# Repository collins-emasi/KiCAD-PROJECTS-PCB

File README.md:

# KiCAD-PROJECTS-PCB
In this repository, I will be sharing some of the project I'm working on with KiCAD software.

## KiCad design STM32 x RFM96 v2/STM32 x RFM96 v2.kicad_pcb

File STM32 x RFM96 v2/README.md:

# STM32 X RFM96 Board
This is an STM32 based board that features semtechs LoRa Chip
Some of the features include
- USB connection
- UART, I2C peripherals
- Battery powered
- LoRa Connectivity
- Ultra low power STM32 chip

# Images

# KiCAD
I am using KiCAD v7.0

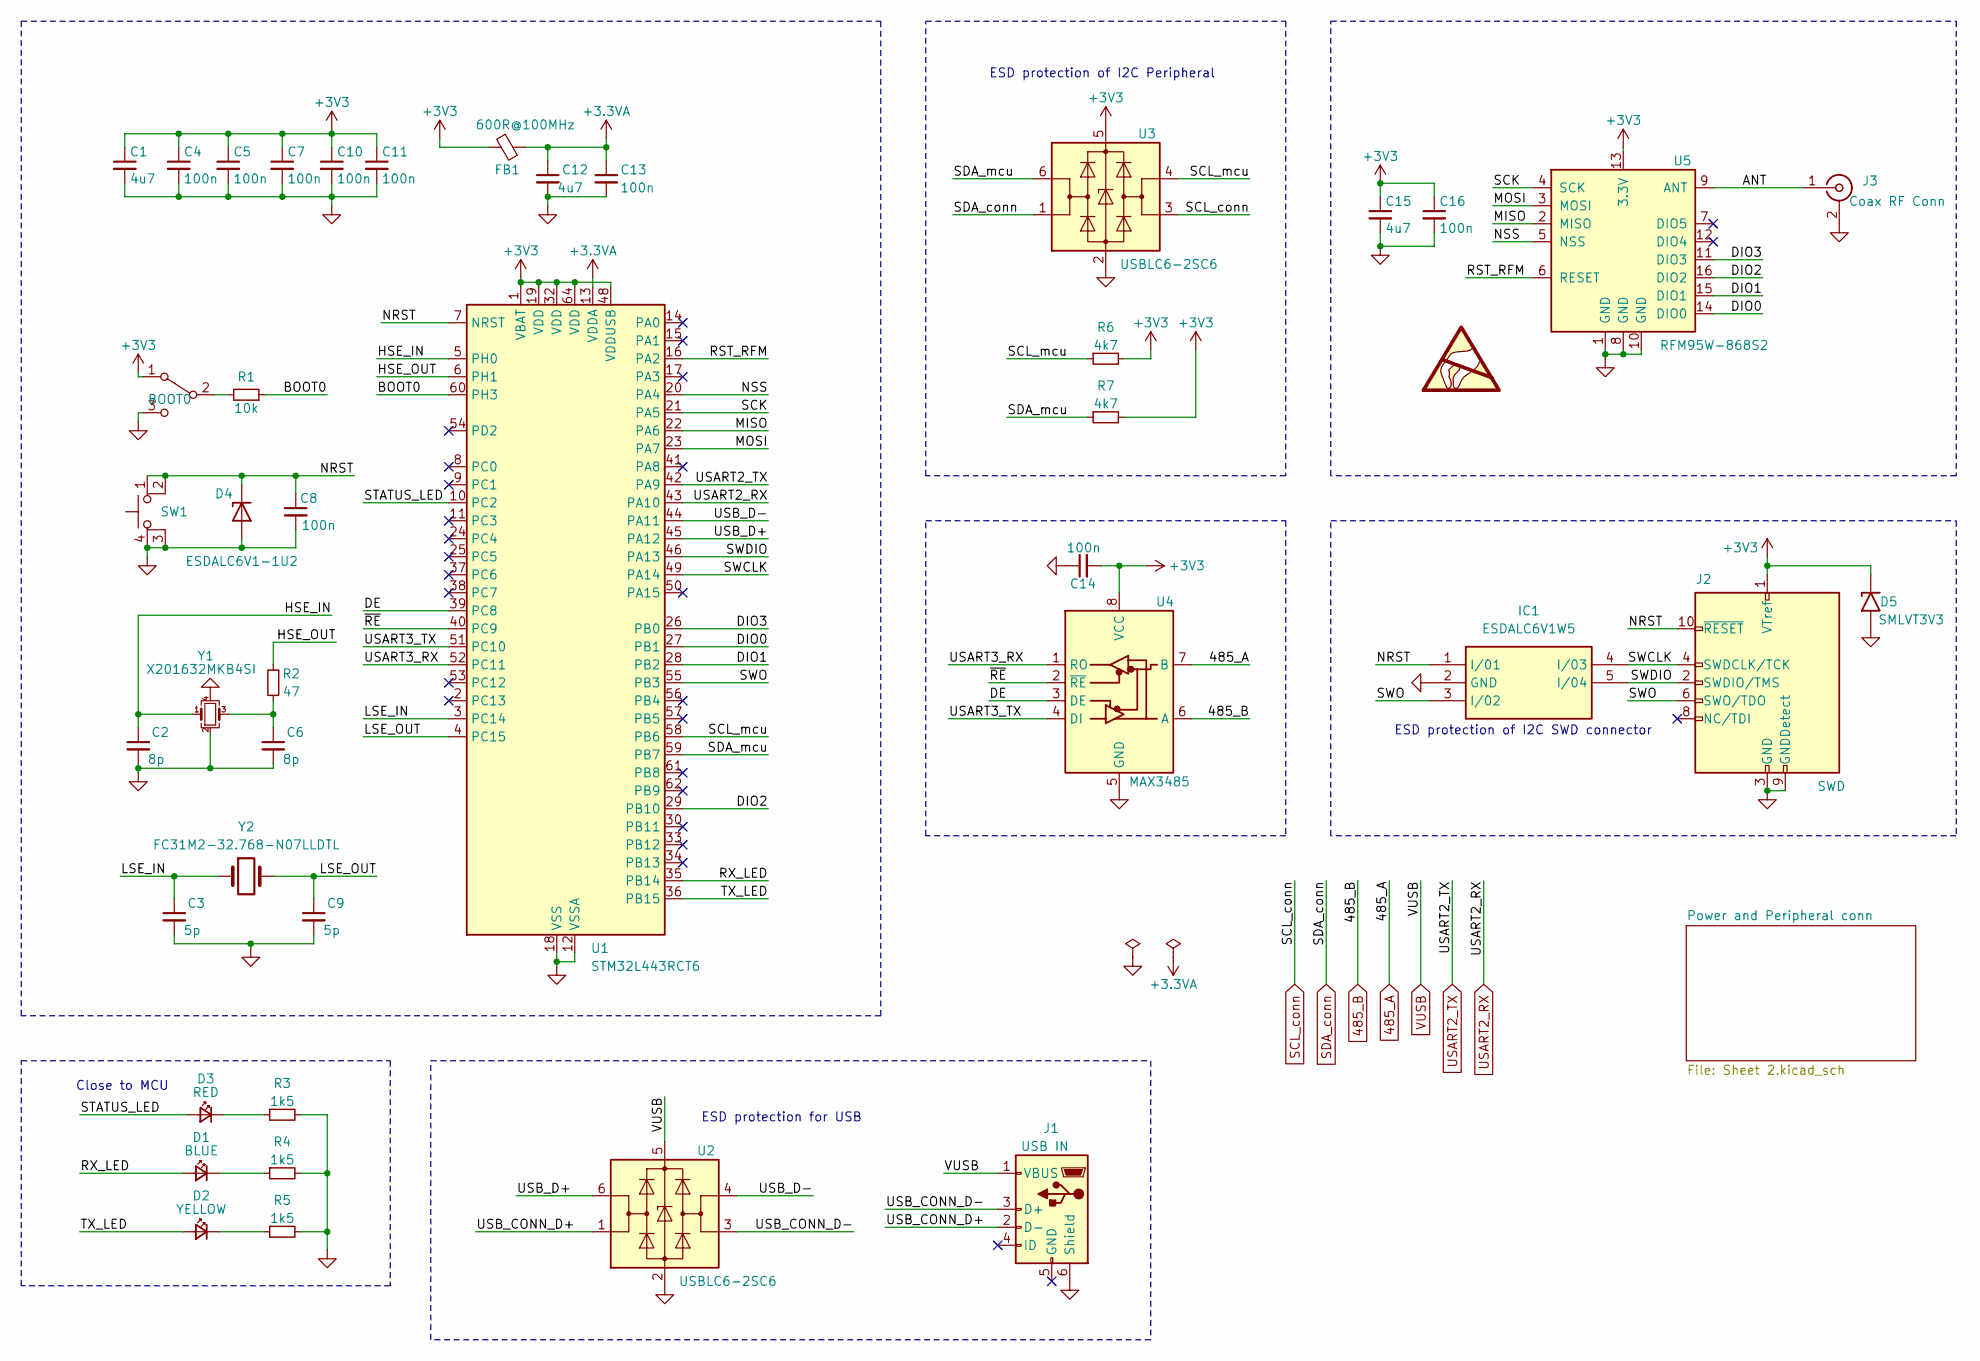
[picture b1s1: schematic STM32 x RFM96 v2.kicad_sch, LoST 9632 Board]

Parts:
BOOT0: SW_SPDT; SW_SPDT_PCM12
C1, C12, C15: 4u7; C_0603_1608Metric
C2, C6: 8p; C_0402_1005Metric
C3, C9: 5p; C_0402_1005Metric
C4, C5, C7, C8, C10, C11, C13, C14, C16: 100n; C_0402_1005Metric
D1: BLUE; LED_0603_1608Metric
D2: YELLOW; LED_0603_1608Metric
D3: RED; LED_0603_1608Metric
D4: ESDALC6V1-1U2; D_SOD-523
D5: SMLVT3V3; SMB
FB1: 600R@100MHz; L_0603_1608Metric
IC1: ESDALC6V1W5; SOT-23-5; Manufacturer_Part_Number ESDALC6V1W5; Mouser Part Number 511-ESDALC6V1W5
J1: USB IN; USB_B_Micro
J2: SWD; PinHeader_2x05_P1.27mm_Vertical
J3: Coax RF Conn; GT-RF1125A-01G
R1: 10k; R_0402_1005Metric
R2: 47; R_0402_1005Metric
R3, R4, R5: 1k5; R_0603_1608Metric
R6, R7: 4k7; R_0603_1608Metric
SW1: SW_MEC_5E; SW4-SMD-5.2X5.2X1.5MM
U1: STM32L443RCT6; LQFP-64_10x10mm_P0.5mm
U2, U3: USBLC6-2SC6; SOT-23-6
U4: MAX3485; SOIC-8_3.9x4.9mm_P1.27mm
U5: RFM95W-868S2; HOPERF_RFM9X
Y1: X201632MKB4SI; Crystal_SMD_2016-4Pin_2.0x1.6mm
Y2: FC31M2-32.768-N07LLDTL; Crystal_SMD_3215-2Pin_3.2x1.5mm

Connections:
485_A: U4.7 (B); also elsewhere on the board
485_B: U4.6 (A); also elsewhere on the board
+3.3VA: C12.1, C13.1, FB1.2, U1.13 (VDDA)
+3V3: BOOT0.1 (A), C1.1, C4.1, C5.1, C7.1, C10.1, C11.1, C14.2, C15.1, C16.1, D5.1 (A1), FB1.1, J2.1 (VTref), R6.2, R7.2, U1.1 (VBAT), U1.19 (VDD), U1.32 (VDD), U1.48 (VDDUSB), U1.64 (VDD), U3.5 (VBUS), U4.8 (VCC), U5.13 (3.3V); also elsewhere on the board
/ANT: J3.1 (In), U5.9 (ANT)
/BOOT0: R1.1, U1.60 (PH3)
/DE: U1.39 (PC8), U4.3 (DE)
/DIO0: U1.27 (PB1), U5.14 (DIO0)
/DIO1: U1.28 (PB2), U5.15 (DIO1)
/DIO2: U1.29 (PB10), U5.16 (DIO2)
/DIO3: U1.26 (PB0), U5.11 (DIO3)
/HSE_IN: C2.1, U1.5 (PH0), Y1.1
/HSE_OUT: R2.1, U1.6 (PH1)
/LSE_IN: C3.1, U1.3 (PC14), Y2.1
/LSE_OUT: C9.1, U1.4 (PC15), Y2.2
/MISO: U1.22 (PA6), U5.2 (MISO)
/MOSI: U1.23 (PA7), U5.3 (MOSI)
/NRST: C8.1, D4.1 (K), IC1.1 (I/01), J2.10 (~RESET), SW1.1, SW1.2, U1.7 (NRST)
/NSS: U1.20 (PA4), U5.5 (NSS)
/RST_RFM: U1.16 (PA2), U5.6 (RESET)
/RX_LED: D1.2 (A), U1.35 (PB14)
/SCK: U1.21 (PA5), U5.4 (SCK)
/SCL_mcu: R6.1, U1.58 (PB6), U3.4 (I/O2)
/SDA_mcu: R7.1, U1.59 (PB7), U3.6 (I/O1)
/STATUS_LED: D3.2 (A), U1.10 (PC2)
/SWCLK: IC1.4 (I/03), J2.4 (SWDCLK/TCK), U1.49 (PA14)
/SWDIO: IC1.5 (I/04), J2.2 (SWDIO/TMS), U1.46 (PA13)
/SWO: IC1.3 (I/02), J2.6 (SWO/TDO), U1.55 (PB3)
/TX_LED: D2.2 (A), U1.36 (PB15)
/USART3_RX: U1.52 (PC11), U4.1 (RO)
/USART3_TX: U1.51 (PC10), U4.4 (DI)
/USB_CONN_D+: J1.2 (D-), U2.1 (I/O1)
/USB_CONN_D-: J1.3 (D+), U2.3 (I/O2)
/USB_D+: U1.45 (PA12), U2.6 (I/O1)
/USB_D-: U1.44 (PA11), U2.4 (I/O2)
/~RE: U1.40 (PC9), U4.2 (~RE)
GND: BOOT0.3 (C), C1.2, C2.2, C3.2, C4.2, C5.2, C6.2, C7.2, C8.2, C9.2, C10.2, C11.2, C12.2, C13.2, C14.1, C15.2, C16.2, D4.2 (A), D5.2 (A2), IC1.2 (GND), J1.6 (Shield), J2.3 (GND), J2.5 (GND), J2.9 (GNDDetect), J3.2 (GND), J3.3 (GND), R3.2, R4.2, R5.2, SW1.3 (K), SW1.4 (A), U1.12 (VSSA), U1.18 (VSS), U1.31 (VSS), U1.47 (VSS), U1.63 (VSS), U2.2 (GND), U3.2 (GND), U4.5 (GND), U5.1 (GND), U5.8 (GND), U5.10 (GND), Y1.2, Y1.4; also elsewhere on the board
unnamed: BOOT0.2 (B), R1.2
unnamed: C6.1, R2.2, Y1.3
unnamed: D1.1 (K), R4.1
unnamed: D2.1 (K), R5.1
unnamed: D3.1 (K), R3.1
USART2_RX: U1.43 (PA10); also elsewhere on the board
USART2_TX: U1.42 (PA9); also elsewhere on the board
VUSB: J1.1 (VBUS), U2.5 (VBUS); also elsewhere on the board

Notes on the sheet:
Close to MCU
ESD protection for USB
ESD protection of I2C Peripheral
ESD protection of I2C SWD connector

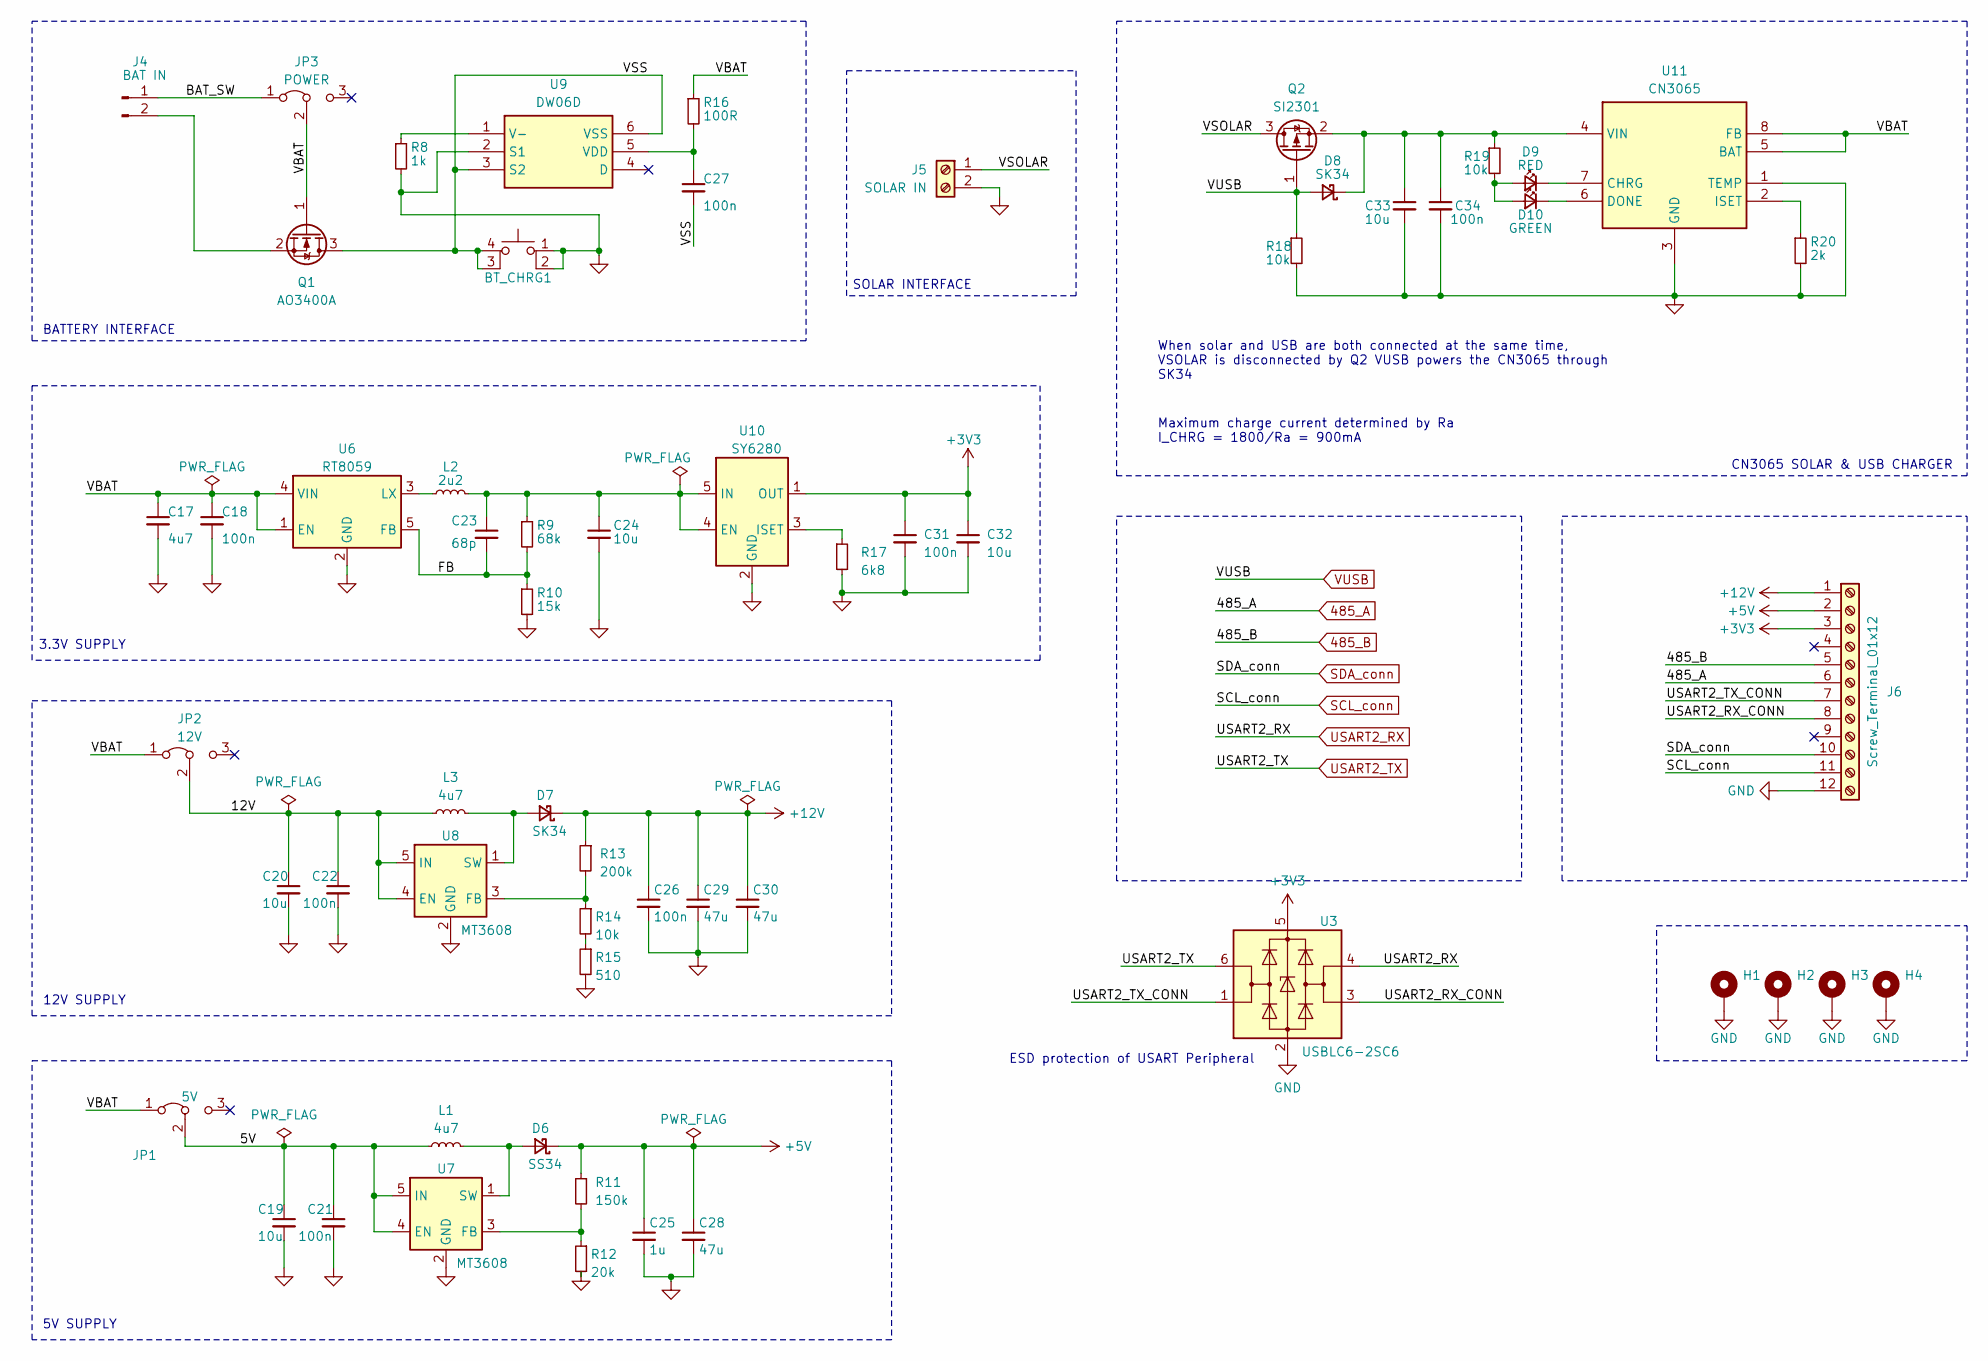
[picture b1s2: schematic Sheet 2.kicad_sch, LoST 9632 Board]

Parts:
BT_CHRG1: SW_MEC_5E; SW4-SMD-5.2X5.2X1.5MM
C17: 4u7; C_0603_1608Metric
C18: 100n; C_0402_1005Metric
C19, C20, C24, C32, C33: 10u; C_0603_1608Metric
C21, C22, C26, C27, C31, C34: 100n; C_0603_1608Metric
C23: 68p; C_0402_1005Metric
C25: 1u; C_0603_1608Metric
C28, C29, C30: 47u; C_0805_2012Metric
D6: SS34; D_0603_1608Metric
D7, D8: SK34; D_0603_1608Metric
D9: RED; LED_0603_1608Metric
D10: GREEN; LED_0603_1608Metric
H1, H2, H3, H4: MountingHole_Pad; MountingHole_2.2mm_M2_Pad
J4: BAT IN; JST_PH_B2B-PH-K_1x02_P2.00mm_Vertical
J5: SOLAR IN; TerminalBlock_Phoenix_MPT-0,5-2-2.54_1x02_P2.54mm_Horizontal
J6: Screw_Terminal_01x12; TerminalBlock_Phoenix_MPT-0,5-12-2.54_1x12_P2.54mm_Horizont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
JP1: 5V; PinHeader_1x03_P2.54mm_Vertical
JP2: 12V; PinHeader_1x03_P2.54mm_Vertical
JP3: POWER; PinHeader_1x03_P2.54mm_Vertical
L1, L3: 4u7; L_Sunlord_SWPA4030S
L2: 2u2; L_Sunlord_SWPA3015S
Q1: AO3400A; SOT-23
Q2: SI2301; SOT-23
R8: 1k; R_0603_1608Metric
R9: 68k; R_0603_1608Metric
R10: 15k; R_0603_1608Metric
R11: 150k; R_0603_1608Metric
R12: 20k; R_0603_1608Metric
R13: 200k; R_0603_1608Metric
R14, R18, R19: 10k; R_0603_1608Metric
R15: 510; R_0603_1608Metric
R16: 100R; R_0603_1608Metric
R17: 6k8; R_0603_1608Metric
R20: 2k; R_0603_1608Metric
U3: USBLC6-2SC6; SOT-23-6
U6: RT8059; SOT-23-5
U7, U8: MT3608; SOT-23-6
U9: DW06D; SOT-23-6; Manufacturer_Part_Number DW06D
U10: SY6280; SOT-23-5
U11: CN3065; SON50P300X300X90-9N-D; Manufacturer_Part_Number CN3065

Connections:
485_A: J6.6; also elsewhere on the board
485_B: J6.5; also elsewhere on the board
+3V3: C31.1, C32.1, J6.3, U3.5 (VBUS), U10.1 (OUT); also elsewhere on the board
+5V: C25.1, C28.1, D6.1 (K), J6.2, R11.1
+12V: C26.1, C29.1, C30.1, D7.1 (K), J6.1, R13.1
/Power and Peripheral conn/5V: C19.1, C21.1, JP1.2 (C), L1.1, U7.4 (EN), U7.5 (IN)
/Power and Peripheral conn/12V: C20.1, C22.1, JP2.2 (C), L3.1, U8.4 (EN), U8.5 (IN)
/Power and Peripheral conn/BAT_SW: J4.1, JP3.1 (A)
/Power and Peripheral conn/FB: C23.2, R9.2, R10.1, U6.5 (FB)
/Power and Peripheral conn/VBAT: C17.1, C18.1, JP1.1 (A), JP2.1 (A), JP3.2 (C), Q1.1 (G), R16.1, U6.1 (EN), U6.4 (VIN), U11.5 (BAT), U11.8 (FB)
/Power and Peripheral conn/VSOLAR: J5.1, Q2.3 (D)
/Power and Peripheral conn/VSS: BT_CHRG1.3 (K), BT_CHRG1.4 (A), C27.2, Q1.3 (D), U9.3 (S2), U9.6 (VSS)
/SCL_mcu: U3.4 (I/O2); also elsewhere on the board
/SDA_mcu: U3.6 (I/O1); also elsewhere on the board
GND: BT_CHRG1.1, BT_CHRG1.2, C17.2, C18.2, C19.2, C20.2, C21.2, C22.2, C24.2, C25.2, C26.2, C28.2, C29.2, C30.2, C31.2, C32.2, C33.2, C34.2, H1.1, H2.1, H3.1, H4.1, J5.2, J6.12, R8.2, R10.2, R12.2, R15.2, R17.2, R18.2, R20.2, U3.2 (GND), U6.2 (GND), U7.2 (GND), U8.2 (GND), U9.2 (S1), U10.2 (GND), U11.1 (TEMP), U11.3 (GND); also elsewhere on the board
unnamed: D6.2 (A), L1.2, U7.1 (SW)
unnamed: D7.2 (A), L3.2, U8.1 (SW)
unnamed: C33.1, C34.1, D8.1 (K), Q2.2 (S), R19.1, U11.4 (VIN)
unnamed: D9.1 (K), U11.7 (CHRG)
unnamed: D9.2 (A), D10.2 (A), R19.2
unnamed: D10.1 (K), U11.6 (DONE)
unnamed: J4.2, Q1.2 (S)
unnamed: R14.2, R15.1
unnamed: L2.1, U6.3 (LX)
unnamed: R11.2, R12.1, U7.3 (FB)
unnamed: R13.2, R14.1, U8.3 (FB)
unnamed: R8.1, U9.1 (V-)
unnamed: C27.1, R16.2, U9.5 (VDD)
unnamed: C23.1, C24.1, L2.2, R9.1, U10.4 (EN), U10.5 (IN)
unnamed: R17.1, U10.3 (ISET)
unnamed: R20.1, U11.2 (ISET)
VUSB: D8.2 (A), Q2.1 (G), R18.1; also elsewhere on the board

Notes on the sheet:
5V SUPPLY
BATTERY INTERFACE
3.3V SUPPLY
ESD protection of USART Peripheral
SOLAR INTERFACE
CN3065 SOLAR & USB CHARGER
12V SUPPLY
Maximum charge current determined by Ra I_CHRG = 1800/Ra = 900mA
When solar and USB are both connected at the same time, VSOLAR is disconnected by Q2 VUSB powers the CN3065 through SK34

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
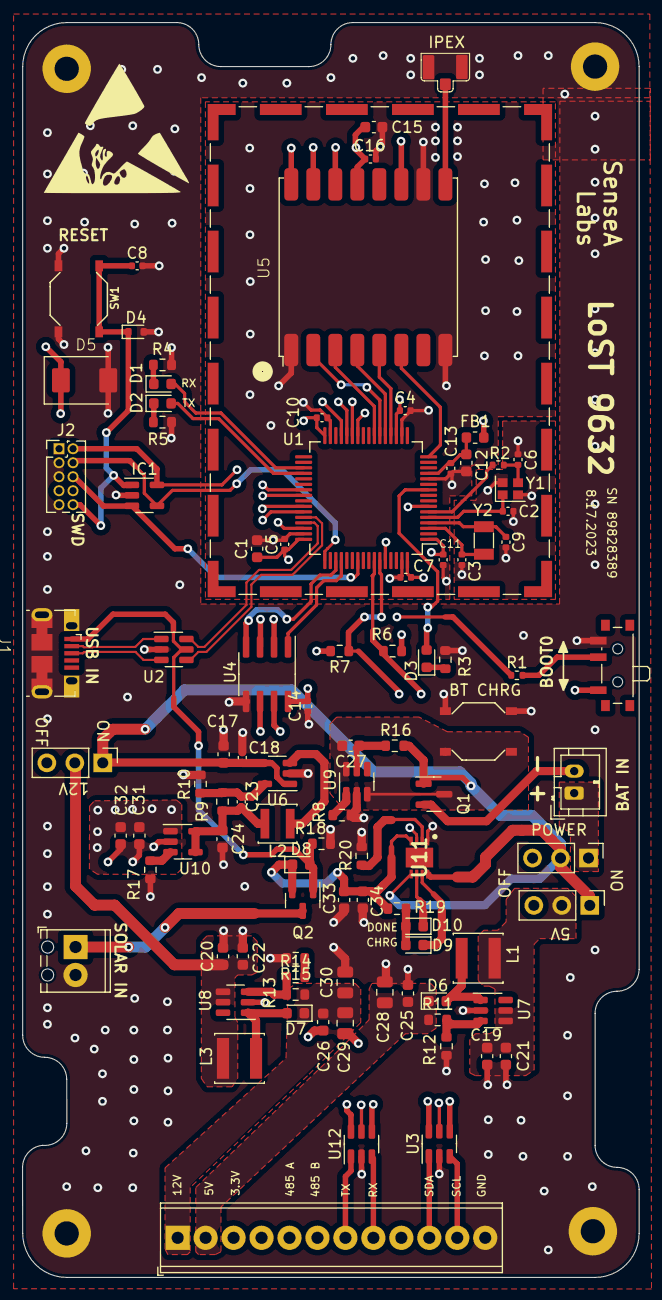
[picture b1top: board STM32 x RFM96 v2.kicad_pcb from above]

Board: 4 copper layers, 56.0 x 114.0 mm, 101 parts (0 on the bottom side), 74 nets.

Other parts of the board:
U12: USBLC6-2SC6; SOT-23-6

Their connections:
+3V3: U12.5 (VBUS); also elsewhere on the board
GND: U12.2 (GND); also elsewhere on the board
USART2_RX: U12.4 (I/O2); also elsewhere on the board
USART2_TX: U12.6 (I/O1); also elsewhere on the board

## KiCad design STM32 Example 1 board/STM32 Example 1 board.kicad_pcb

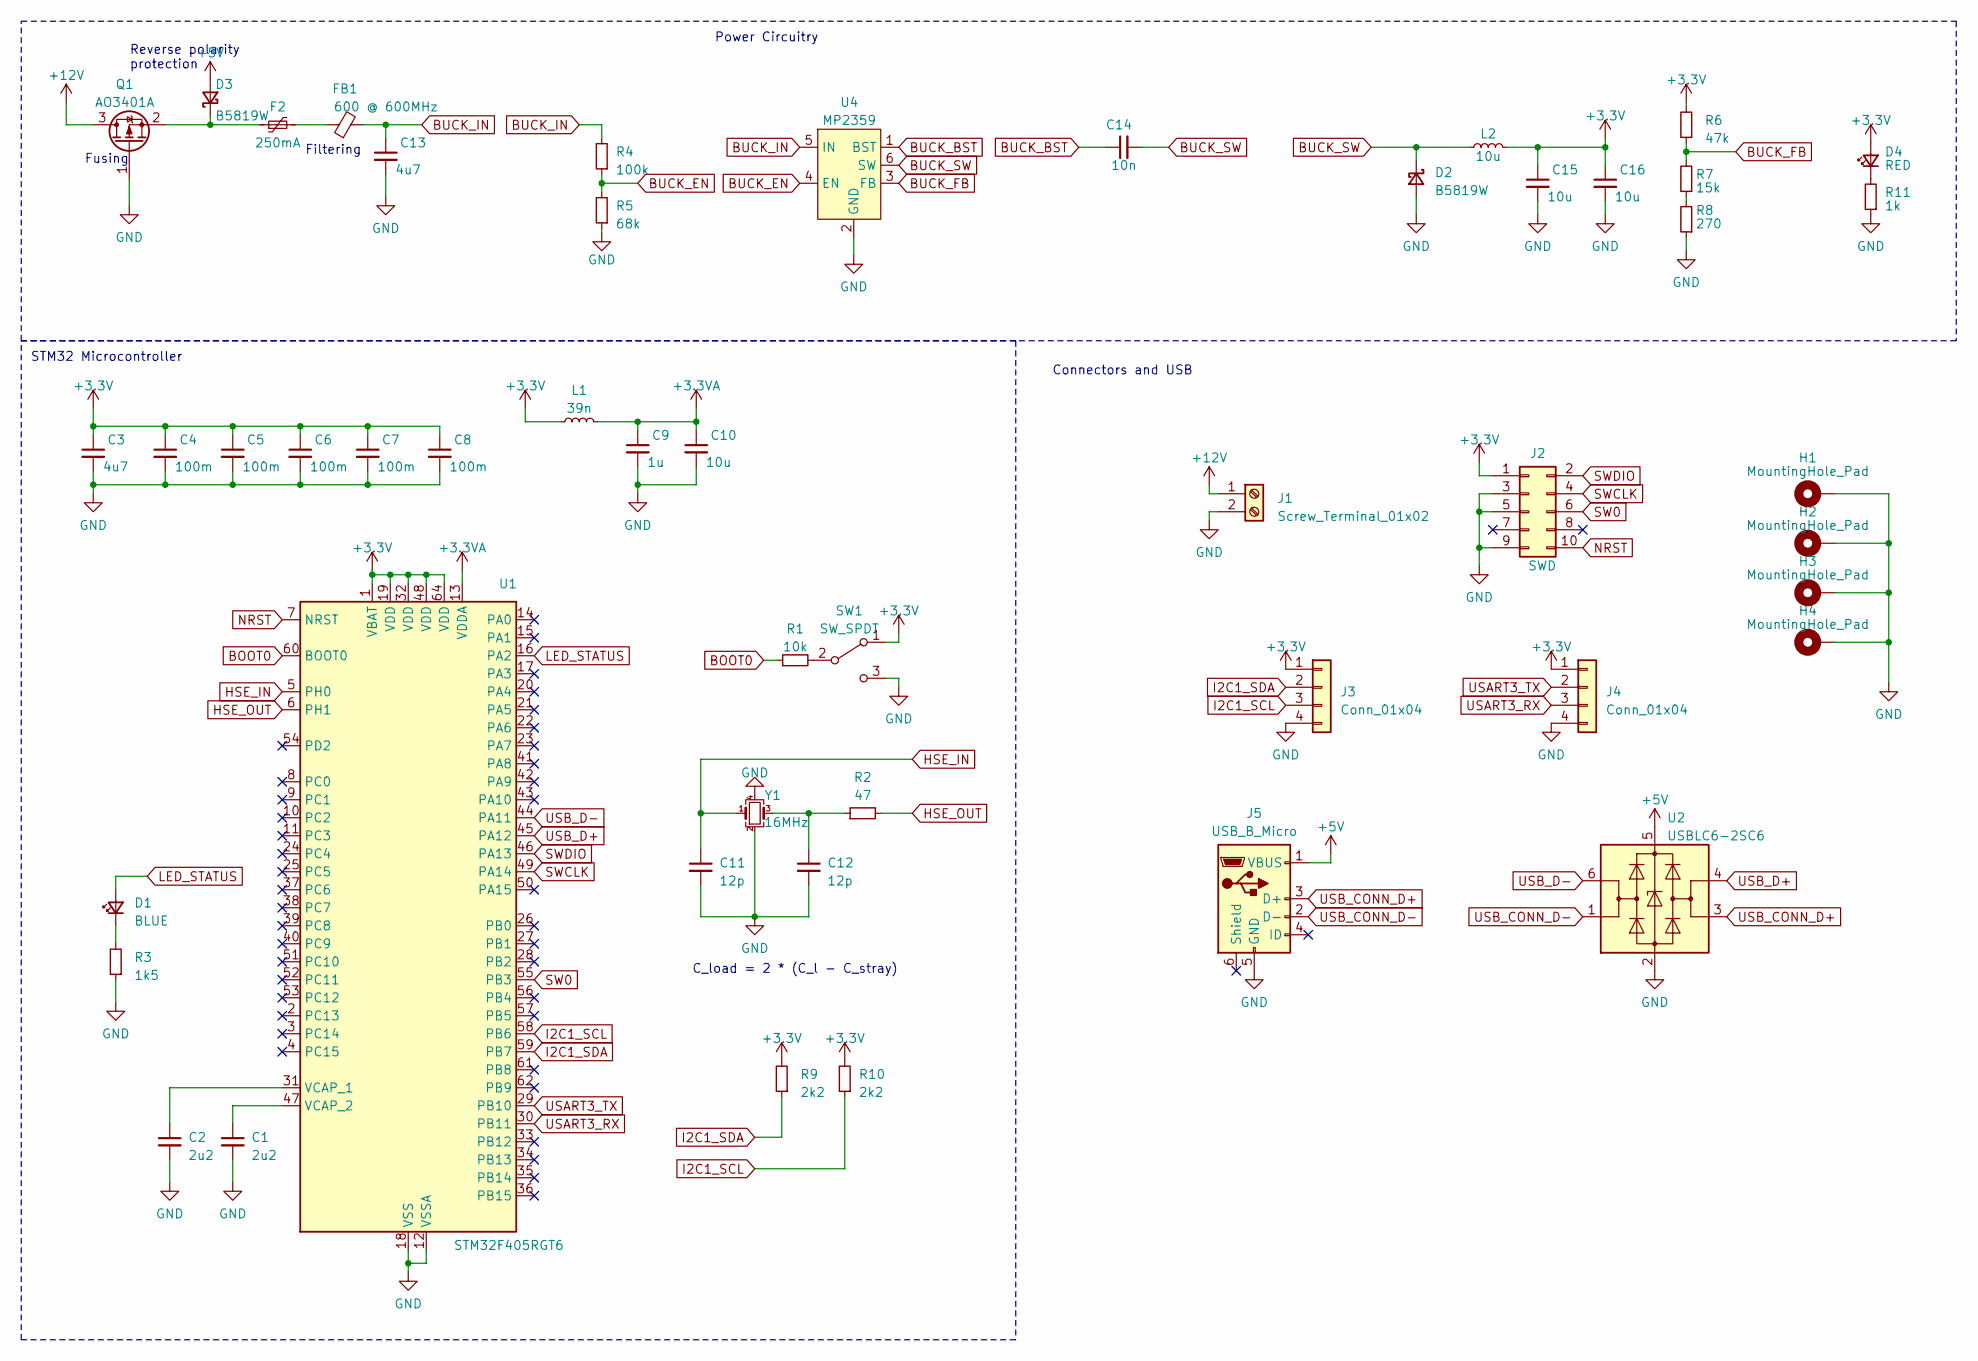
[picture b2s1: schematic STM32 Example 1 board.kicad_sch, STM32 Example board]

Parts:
C1, C2: 2u2; C_0603_1608Metric
C3, C13: 4u7; C_0603_1608Metric
C4, C5, C6, C7, C8: 100m; C_0402_1005Metric
C9: 1u; C_0402_1005Metric
C10, C15, C16: 10u; C_1206_3216Metric
C11, C12: 12p; C_0402_1005Metric
C14: 10n; C_0603_1608Metric
D1: BLUE; D_0603_1608Metric
D2, D3: B5819W; D_SOD-123
D4: RED; D_0603_1608Metric
F2: 250mA; Fuse_1206_3216Metric
FB1: 600 @ 600MHz; L_0805_2012Metric
H1, H2, H3, H4: MountingHole_Pad; MountingHole_4.3mm_M4_Pad_Via
J1: Screw_Terminal_01x02; TerminalBlock_Phoenix_PT-1,5-2-3.5-H_1x02_P3.50mm_Horizontal
J2: SWD; PinSocket_2x05_P1.27mm_Vertical_SMD
J3, J4: Conn_01x04; Molex_PicoBlade_53048-0410_1x04_P1.25mm_Horizontal
J5: USB_B_Micro; USB_Micro-B_Amphenol_10104110_Horizontal
L1: 39n; L_0402_1005Metric
L2: 10u; L_Sunlord_MWSA0518S
Q1: AO3401A; SOT-23
R1: 10k; R_0402_1005Metric
R2: 47; R_0402_1005Metric
R3: 1k5; R_0603_1608Metric
R4: 100k; R_0603_1608Metric
R5: 68k; R_0603_1608Metric
R6: 47k; R_0603_1608Metric
R7: 15k; R_0603_1608Metric
R8: 270; R_0603_1608Metric
R9, R10: 2k2; R_0402_1005Metric
R11: 1k; R_0603_1608Metric
SW1: SW_SPDT; SW_SPDT_PCM12
U1: STM32F405RGT6; LQFP-64_10x10mm_P0.5mm
U2: USBLC6-2SC6; SOT-23-6
U4: MP2359; SOT-23-6
Y1: 16MHz; Crystal_SMD_3225-4Pin_3.2x2.5mm

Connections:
+3.3V: C3.1, C4.1, C5.1, C6.1, C7.1, C8.1, C15.1, C16.1, D4.2 (A), J2.1, J3.1, J4.1, L1.1, L2.2, R6.2, R9.2, R10.2, SW1.1 (A), U1.1 (VBAT), U1.19 (VDD), U1.32 (VDD), U1.48 (VDD), U1.64 (VDD)
+3.3VA: C9.1, C10.1, L1.2, U1.13 (VDDA)
+5V: D3.2 (A), J5.1 (VBUS), U2.5 (VBUS)
+12V: J1.1, Q1.3 (D)
BOOT0: R1.1, U1.60 (BOOT0)
BUCK_BST: C14.1, U4.1 (BST)
BUCK_EN: R4.1, R5.2, U4.4 (EN)
BUCK_FB: R6.1, R7.2, U4.3 (FB)
BUCK_IN: C13.1, FB1.2, R4.2, U4.5 (IN)
BUCK_SW: C14.2, D2.1 (K), L2.1, U4.6 (SW)
GND: C1.2, C2.2, C3.2, C4.2, C5.2, C6.2, C7.2, C8.2, C9.2, C10.2, C11.2, C12.2, C13.2, C15.2, C16.2, D2.2 (A), H1.1, H2.1, H3.1, H4.1, J1.2, J2.3, J2.5, J2.9, J3.4, J4.4, J5.5 (GND), Q1.1 (G), R3.1, R5.1, R8.1, R11.1, SW1.3 (C), U1.12 (VSSA), U1.18 (VSS), U1.63 (VSS), U2.2 (GND), U4.2 (GND), Y1.2, Y1.4
HSE_IN: C11.1, U1.5 (PH0), Y1.1
HSE_OUT: R2.2, U1.6 (PH1)
I2C1_SCL: J3.3, R10.1, U1.58 (PB6)
I2C1_SDA: J3.2, R9.1, U1.59 (PB7)
LED_STATUS: D1.2 (A), U1.16 (PA2)
NRST: J2.10, U1.7 (NRST)
unnamed: C12.1, R2.1, Y1.3
unnamed: D1.1 (K), R3.2
unnamed: D3.1 (K), F2.1, Q1.2 (S)
unnamed: D4.1 (K), R11.2
unnamed: F2.2, FB1.1
unnamed: R7.1, R8.2
unnamed: R1.2, SW1.2 (B)
unnamed: C2.1, U1.31 (VCAP_1)
unnamed: C1.1, U1.47 (VCAP_2)
SW0: J2.6, U1.55 (PB3)
SWCLK: J2.4, U1.49 (PA14)
SWDIO: J2.2, U1.46 (PA13)
USART3_RX: J4.3, U1.30 (PB11)
USART3_TX: J4.2, U1.29 (PB10)
USB_CONN_D+: J5.3 (D+), U2.3 (I/O2)
USB_CONN_D-: J5.2 (D-), U2.1 (I/O1)
USB_D+: U1.45 (PA12), U2.4 (I/O2)
USB_D-: U1.44 (PA11), U2.6 (I/O1)

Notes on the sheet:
STM32 Microcontroller
Power Circuitry
Filtering
Reverse polarity protection
C_load = 2 * (C_l - C_stray)
Fusing
Connectors and USB

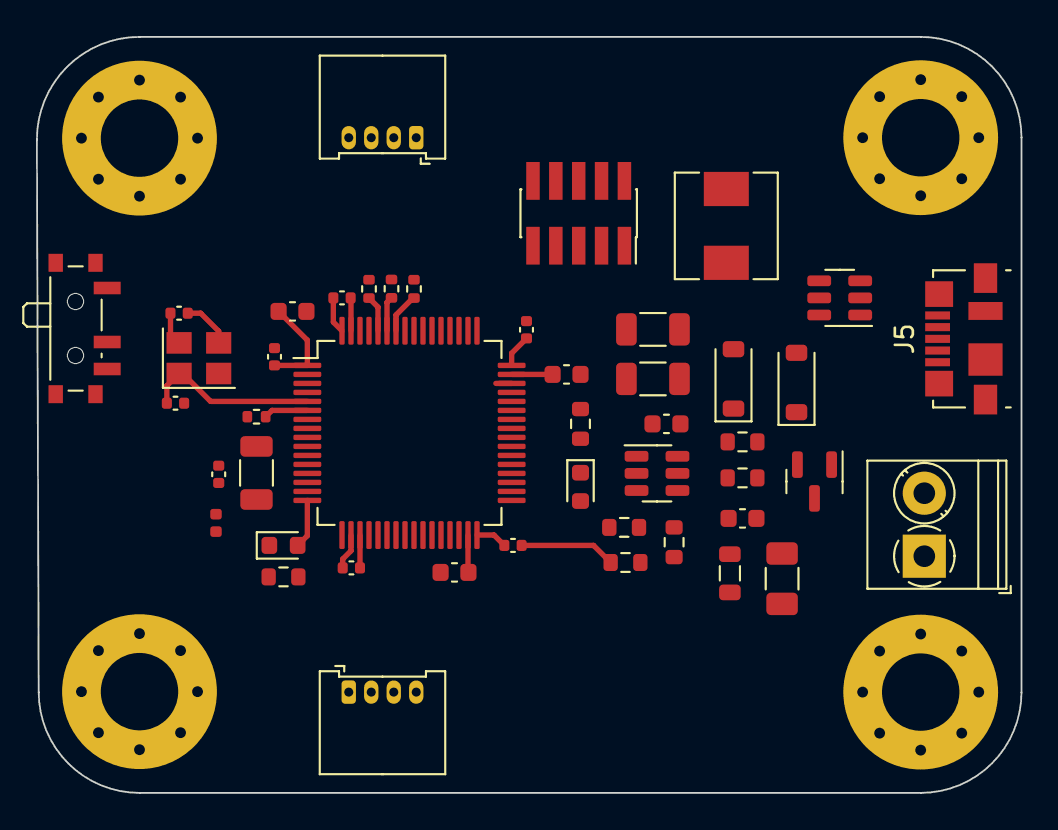
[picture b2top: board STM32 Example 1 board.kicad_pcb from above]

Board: 4 copper layers, 54.7 x 42.0 mm, 50 parts (0 on the bottom side), 35 nets.

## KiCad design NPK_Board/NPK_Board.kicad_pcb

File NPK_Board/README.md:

# NPK Board
Project is still under development

# KiCAD
I am using KiCAD v7.0

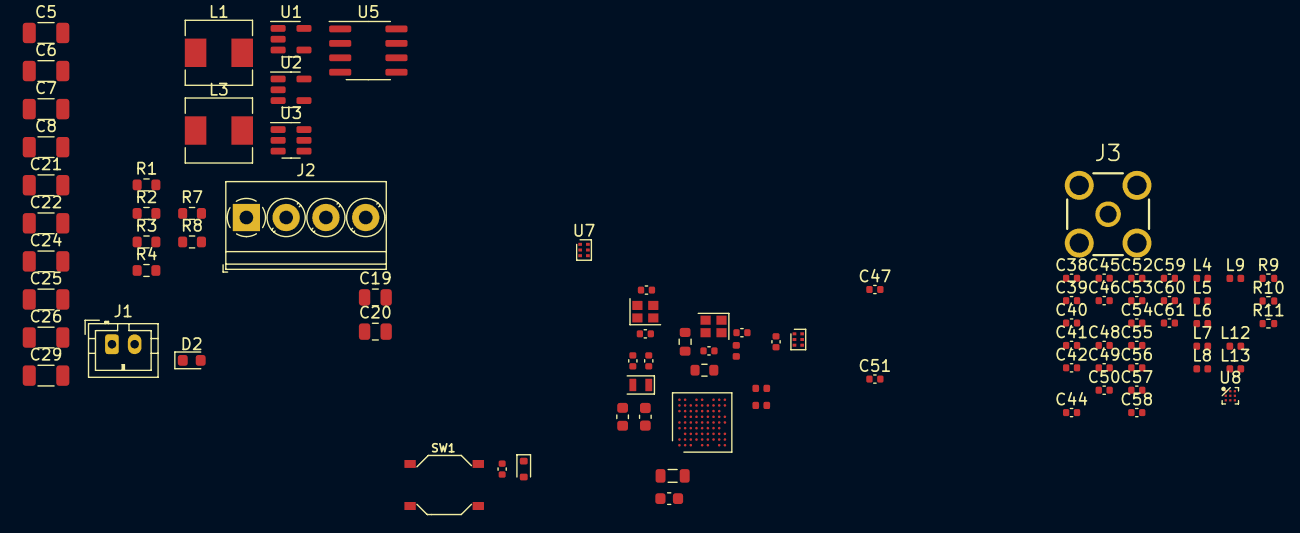
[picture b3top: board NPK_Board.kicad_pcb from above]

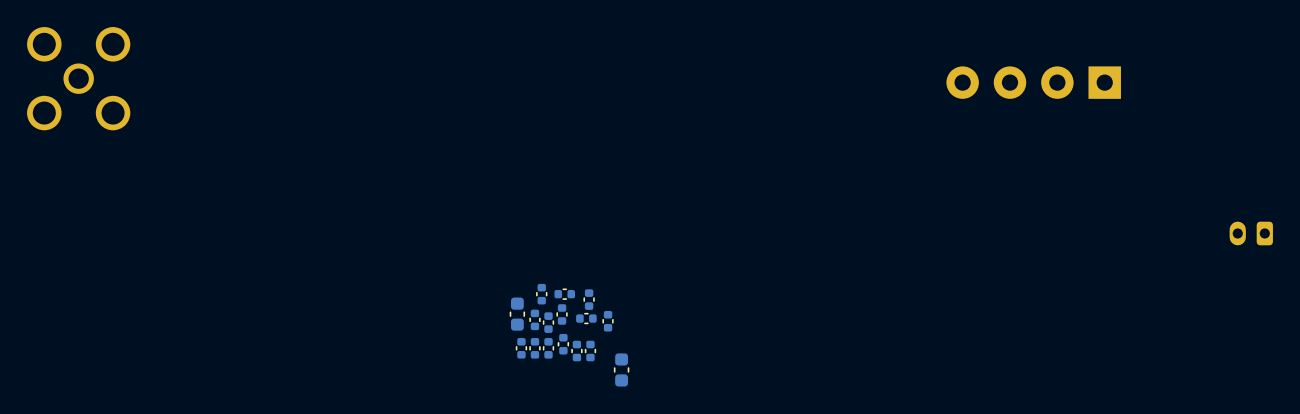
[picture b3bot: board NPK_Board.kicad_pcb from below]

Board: 4 copper layers, 104 parts (16 on the bottom side), 55 nets, no tracks yet.

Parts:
C1, C9, C16: 4u7; C_0603_1608Metric
C2, C10, C11, C12, C13, C14, C15, C18, C33: 100n; C_0402_1005Metric
C3: 3.3p; C_0402_1005Metric
C4, C34, C35, C52, C59: 33p; C_0402_1005Metric
C5: 68p; C_1206_3216Metric
C6, C21: 10u; C_1206_3216Metric
C7: 4u7; C_1206_3216Metric
C8, C22, C24, C29: 100n; C_1206_3216Metric
C17: 470n; C_0603_1608Metric
C19: 10u; C_0805_2012Metric
C20: 100n; C_0805_2012Metric
C23: 10p; C_0402_1005Metric
C25, C26: 47u; C_1206_3216Metric
C27: 220n; C_0402_1005Metric
C28, C30: 5.1p; C_0402_1005Metric
C31, C32: 6.8p; C_0402_1005Metric
C36: 47p; C_0402_1005Metric
C37, C43, C44, C45: 1p2; C_0402_1005Metric
C38, C40, C41: 1n; C_0402_1005Metric
C39: 2p2; C_0402_1005Metric
C42, C47, C49, C51: 68p; C_0402_1005Metric
C46, C54: 5p6; C_0402_1005Metric
C48: 47n; C_0402_1005Metric
C50, C58: 2p7; C_0402_1005Metric
C53: 1p3; C_0402_1005Metric
C55, C60, C61: 3p3; C_0402_1005Metric
C56: 3p6; C_0402_1005Metric
C57: 1p; C_0402_1005Metric
D1: ESDALC6V1-1U2; D_SOD-523
D2: SK34; D_0603_1608Metric
FB1: 600R@100MHz; L_0603_1608Metric
FB2: 1400R@1GHz; L_0402_1005Metric
J1: Battery Conn; JST_PH_B2B-PH-K_1x02_P2.00mm_Vertical
J2: Screw_Terminal_01x04; TerminalBlock_Phoenix_PT-1,5-4-3.5-H_1x04_P3.50mm_Horizontal
J3: SMA; SMA CONNECTOR JACK
L1, L3: 2u2; L_Sunlord_MWSA0503S
L2: 15u; L_0805_2012Metric
L4, L10: 3n6; L_0402_1005Metric
L5, L9, L13: 8n7; L_0402_1005Metric
L6: 33n; L_0402_1005Metric
L7: 47n; L_0402_1005Metric
L8: 3n; L_0402_1005Metric
L11: 3n3; L_0402_1005Metric
L12: 11n; L_0402_1005Metric
R1: 68k; R_0603_1608Metric
R2: 15k; R_0603_1608Metric
R3: 6k8; R_0603_1608Metric
R4, R6: 200k; R_0603_1608Metric
R5, R7: 10k; R_0603_1608Metric
R8: 510; R_0603_1608Metric
R9, R10, R11: 100R; R_0402_1005Metric
SW1: SW_MEC_5E; SW4-SMD-5.2X5.2X1.5MM
U1: RT8059; SOT-23-5
U2: SOT-23-5
U3: MT3608; SOT-23-6
U4: STM32WL55JCI7; ST_UFBGA-73_5x5mm_Layout9x9_P0.5mm
U5: MAX3485; SOIC-8_3.9x4.9mm_P1.27mm
U6, U7: NX3L1T3157; SOT-886
U8: BGS13S4N9; TSNP-9_3x3_1.2x1.2mm
Y2: 32.768KHz; Crystal_SMD_2012-2Pin_2.0x1.6mm_3D
Y3, Y4: 32MHz; Crystal_SMD_2016-4Pin_2.0x1.6mm

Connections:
485_A: J2.2, U5.6 (A)
485_B: J2.3, U5.7 (B)
+12V: C24.1, C25.1, C26.1, D2.1 (K), J2.1, R4.1
/DE: U4.J1 (PA4), U5.3 (DE)
/FB: C5.2, R1.2, R2.1, U1.5 (FB)
/LPUART1_RX: U4.H1 (PA3), U5.1 (RO)
/LPUART1_TX: U4.H2 (PA2), U5.4 (DI)
/OSC_LS_IN: C28.2, U4.B6 (PC14), Y2.2
/OSC_LS_OUT: C30.2, U4.C5 (PC15), Y2.1
/~RE: U4.J2 (PA5), U5.2 (~RE)
FE_CTRL1: R10.1, U4.F3 (PC4), U6.6 (SEL), U7.6 (SEL)
FE_CTRL2: R9.1, U4.E4 (PC5)
FE_CTRL3: R11.1, U4.D5 (PC3)
GND: C1.2, C2.2, C3.2, C4.2, C6.2, C7.2, C8.2, C9.2, C10.2, C11.2, C12.2, C13.2, C14.2, C15.2, C16.1, C17.2, C18.2, C19.2, C20.2, C21.2, C22.2, C24.2, C25.2, C26.2, C27.2, C28.1, C29.1, C30.1, C31.2, C32.2, C33.2, C34.2, C35.2, C36.2, C37.2, C38.2, C40.2, C41.2, C43.2, C44.2, C45.1, C46.1, C47.1, C48.2, C49.2, C51.2, C53.2, C54.1, C55.1, C57.2, C58.1, C60.1, C61.1, D1.2 (A), J1.2, J2.4, J3.2 (Ext), R2.2, R3.2, R5.2, R8.2, SW1.3 (K), SW1.4 (A), U1.2 (GND), U2.2 (GND), U3.2 (GND), U4.A1 (VSSSMPS), U4.B7 (VSS), U4.D9 (VSS), U4.E3 (VSS), U4.G5 (VSS), U4.G6 (VSSRF), U4.G7 (VSSRF), U4.G8 (VSSRF), U4.H6 (VSSRF), U5.5 (GND), U6.2 (GND), U7.2 (GND), U8.6 (DGND), U8.9 (GND), Y3.2, Y3.4, Y4.1 (EN), Y4.2 (GND)
NRST: C18.1, D1.1 (K), SW1.1, SW1.2, U4.F5 (NRST)
unnamed: C23.1, R6.2
unnamed: C39.1, C45.2, L4.1, L6.2, L10.2
unnamed: C39.2, C42.2, C46.2, L4.2
unnamed: C42.1, L5.1
unnamed: C50.1, C54.2, L7.2, L8.1, L11.2
unnamed: C50.2, C52.2, C55.2, L8.2
unnamed: C52.1, L9.1
unnamed: C59.1, C61.2, L13.2
unnamed: D2.2 (A), L3.2, U3.1 (SW)
unnamed: C60.2, J3.1 (In), L13.1
unnamed: R7.2, R8.1
unnamed: L1.1, U1.3 (LX)
unnamed: C5.1, C6.1, L1.2, R1.1, U2.4 (EN), U2.5 (IN)
unnamed: R3.1, U2.3 (ISET)
unnamed: R4.2, R7.1, U3.3 (FB)
unnamed: L2.2, U4.B1 (VLXSMPS)
unnamed: C47.2, L6.1, U7.3 (Y0)
unnamed: C51.1, L7.1, U7.1 (Y1)
unnamed: C56.1, C57.1, U8.3 (RF1)
unnamed: C44.1, L5.2, U8.5 (RF2)
unnamed: C53.1, L9.2, U8.2 (RF3)
unnamed: C59.2, U8.4 (RF_in)
unnamed: C40.1, R10.2, U8.1 (V1)
unnamed: C38.1, R9.2, U8.8 (V2)
unnamed: C41.1, R11.2, U8.7 (VDD)
unnamed: R6.1, Y4.3 (OUT)
unnamed: C27.1, FB2.2, Y4.4 (VDD)
OSC_HS_IN: C23.2, C31.1, R5.1, U4.G9 (OSC_IN), Y3.1
OSC_HS_OUT: C32.1, U4.F8 (OSC_OUT), Y3.3
RFI+: C56.2, L12.2, U4.J6 (RFI_P)
RFI-: C58.2, L12.1, U4.H7 (RFI_N)
RFO_HP: L10.1, U4.J9 (RFO_HP)
RFO_LP: L11.1, U4.J8 (RFO_LP)
VBAT: C7.1, C8.1, C21.1, C22.1, J1.1, L3.1, U1.1 (EN), U1.4 (VIN), U3.4 (EN), U3.5 (IN)
VDDPA: C34.1, U4.H8 (VDDPA), U6.4 (Z)
VDDRF1V55: C17.1, C35.1, L2.1, U4.B2 (VFBSMPS), U4.F7 (VDDRF1V55), U6.1 (Y1)
VDD_SYS: C3.1, C4.1, C9.1, C10.1, C11.1, C12.1, C13.1, C14.1, C15.1, C16.2, C19.1, C20.1, C29.2, FB1.1, U2.1 (OUT), U4.A2 (VDDSMPS), U4.A7 (VDD), U4.A8 (VBAT), U4.E2 (VDD), U4.E8 (VDDRF), U4.E9 (VDD), U4.H5 (VDD), U5.8 (VCC), U6.3 (Y0), U6.5 (VCC), U7.5 (VCC)
VDD_TCX0: C33.1, C36.1, C37.1, FB2.1, U4.F6 (PB0)
VREF: C1.1, C2.1, FB1.2, U4.A5 (VDDA), U4.B5 (VREF+)
VR_PA: C43.1, C48.1, C49.1, U4.H9 (VR_PA), U7.4 (Z)
